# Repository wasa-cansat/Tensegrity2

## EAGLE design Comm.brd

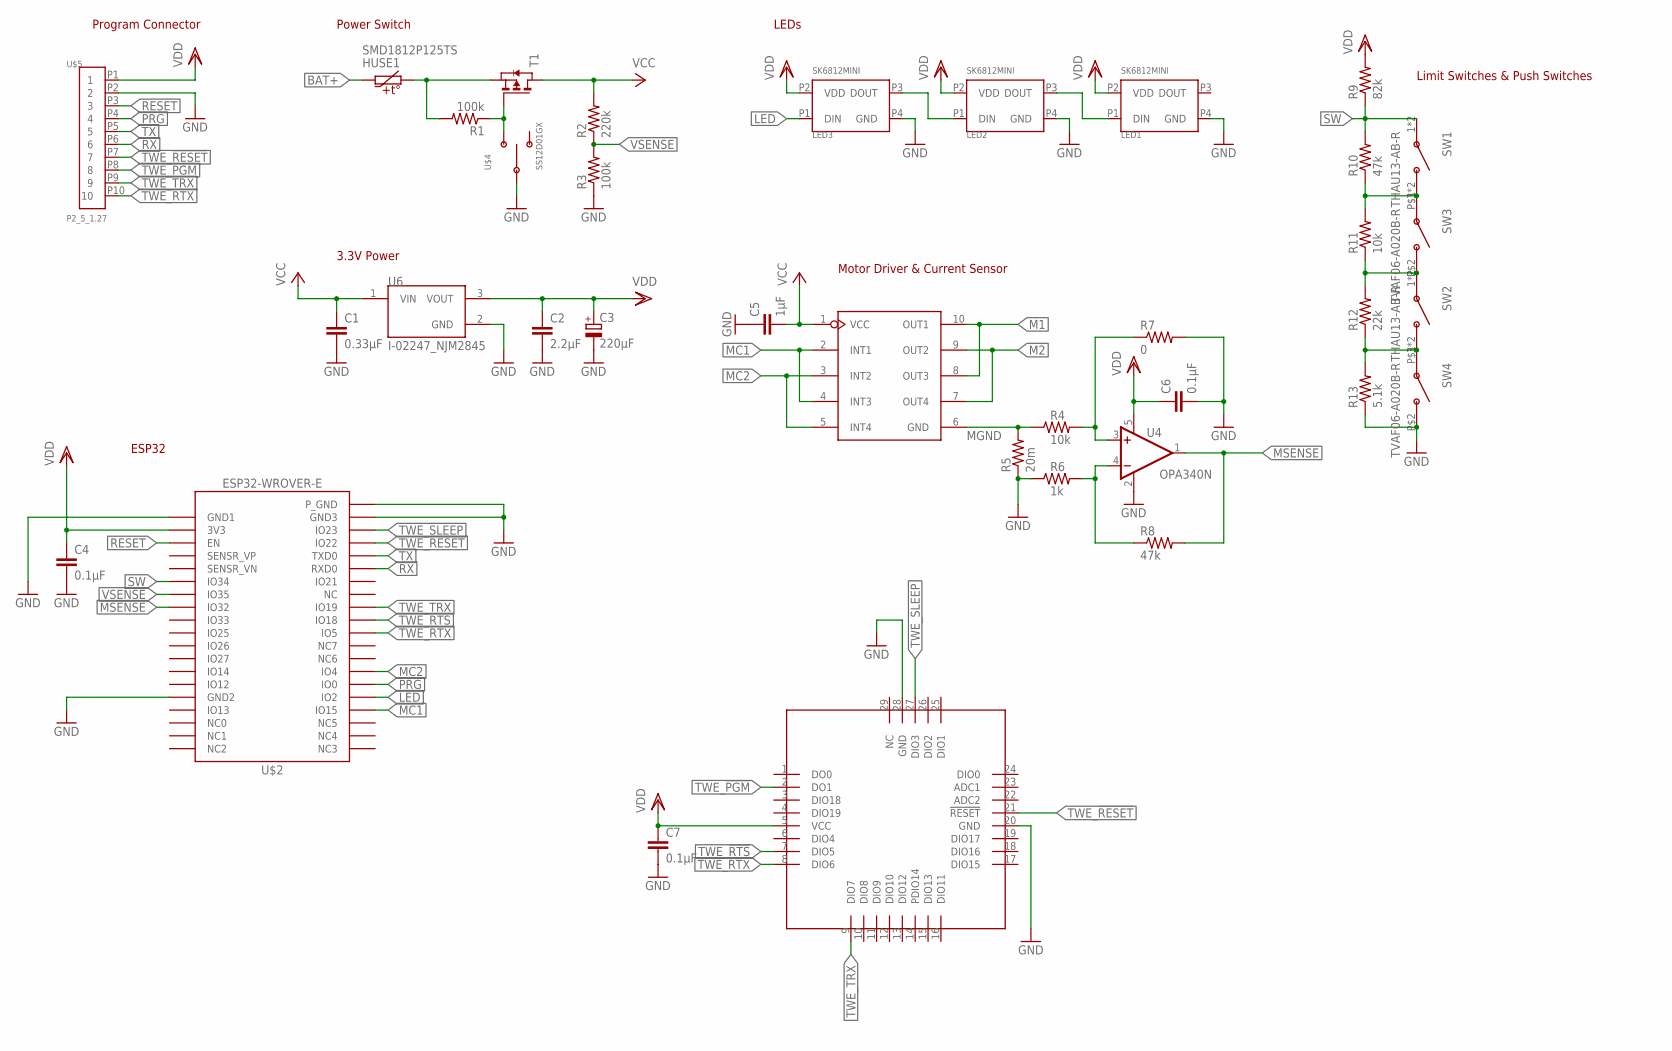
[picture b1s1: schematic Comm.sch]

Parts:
C1: 0.33µF; C0603
C2: 2.2µF; C0603
C3: 220µF; UD-6,3X7,7_NICHICON
C4, C6: 0.1µF; C0603
C5: 1µF; C0603
C7: 0.1µF; C0603K
HUSE1: SMD1812P125TS; SMD1812P
LED1, LED2, LED3: SK6812MINI; SK68XXMINI
R1, R3: 100k; R0603
R2: 220k; R0603
R4, R11: 10k; R0603
R5: 20m; R6332W
R6: 1k; R0603
R7: 0; R0603
R8, R10: 47k; R0603
R9: 82k; R0603
R12: 22k; R0603
R13: 5.1k; R0603
SW1, SW2: THAU13-AB-R
SW3, SW4: TVAF06-A020B-R
T1: PMOSSOT23; SOT-23
TWE-LITE: LITE
U4: OPA340N; SOT23-5
U5: DRIVER-LV8548MC-AH(SOIC10); SOIC10-1.0-5X4MM
U6: I-02247_NJM2845; TO252
U$2: ESP32-WROVER-E
U$4: SS12D01GX
U$5: P2_5_1.27

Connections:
BAT+: HUSE1.1
GND: C1.2, C2.2, C3.-, C4.2, C5.1, C6.2, C7.2, LED1.P4 (GND), LED2.P4 (GND), LED3.P4 (GND), R3.1, R5.1, R6.1, R7.2, R13.1, SW4.P$2 (B), TWE-LITE.20 (GND), TWE-LITE.28 (GND), U4.2 (V-), U6.2 (GND), U$2.GND1, U$2.GND2, U$2.GND3, U$2.P_GND, U$4.2 (C), U$5.P2 (2)
LED: LED3.P1 (DIN), U$2.IO2
M1: U5.8 (OUT3), U5.10 (OUT1)
M2: U5.7 (OUT4), U5.9 (OUT2)
MC1: U5.2 (INT1), U5.4 (INT3), U$2.IO15
MC2: U5.3 (INT2), U5.5 (INT4), U$2.IO4
MGND: R4.1, R5.2, U5.6 (GND)
MSENSE: R8.2, U4.1 (OUT), U$2.IO32
unnamed: HUSE1.2, R1.2, T1.2 (S)
unnamed: R6.2, R8.1, U4.4 (-IN)
unnamed: R4.2, R7.1, U4.3 (+IN)
unnamed: R1.1, T1.3 (G), U$4.1 (A)
unnamed: LED2.P1 (DIN), LED3.P3 (DOUT)
unnamed: LED1.P1 (DIN), LED2.P3 (DOUT)
unnamed: R11.1, R12.2, SW2.1 (A), SW2.2 (A), SW3.P$2 (B)
unnamed: R10.1, R11.2, SW1.3 (B), SW1.4 (B), SW3.P$1 (A)
unnamed: R12.1, R13.2, SW2.3 (B), SW2.4 (B), SW4.P$1 (A)
PRG: U$2.IO0, U$5.P4 (4)
RESET: U$2.EN, U$5.P3 (3)
RX: U$2.RXD0, U$5.P6 (6)
SW: R9.1, R10.2, SW1.1 (A), SW1.2 (A), U$2.IO34
TWE_!PGM!: TWE-LITE.2 (DO1), U$5.P8 (8)
TWE_!RESET!: TWE-LITE.21 (!RESET!), U$2.IO22, U$5.P7 (7)
TWE_!RTS!: TWE-LITE.7 (DIO5), U$2.IO18
TWE_RTX: TWE-LITE.8 (DIO6), U$2.IO5, U$5.P10 (10)
TWE_SLEEP: TWE-LITE.27 (DIO3), U$2.IO23
TWE_TRX: TWE-LITE.9 (DIO7), U$2.IO19, U$5.P9 (9)
TX: U$2.TXD0, U$5.P5 (5)
VCC: C1.1, C5.2, R2.2, T1.1 (D), U5.1 (VCC), U6.1 (VIN)
VDD: C2.1, C3.+, C4.1, C6.1, C7.1, LED1.P2 (VDD), LED2.P2 (VDD), LED3.P2 (VDD), R9.2, TWE-LITE.5 (VCC), U4.5 (V+), U6.3 (VOUT), U$2.3V3, U$5.P1 (1)
VSENSE: R2.1, R3.2, U$2.IO35

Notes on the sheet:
Program Connector
Power Switch
3.3V Power
Motor Driver & Current Sensor
ESP32
LEDs
Limit Switches & Push Switches

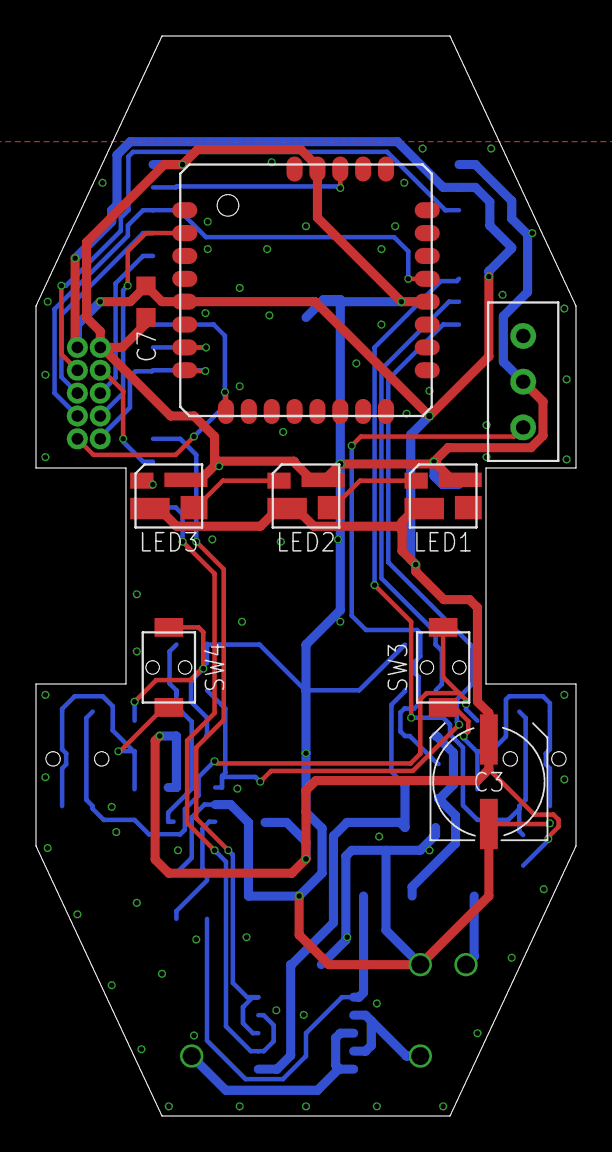
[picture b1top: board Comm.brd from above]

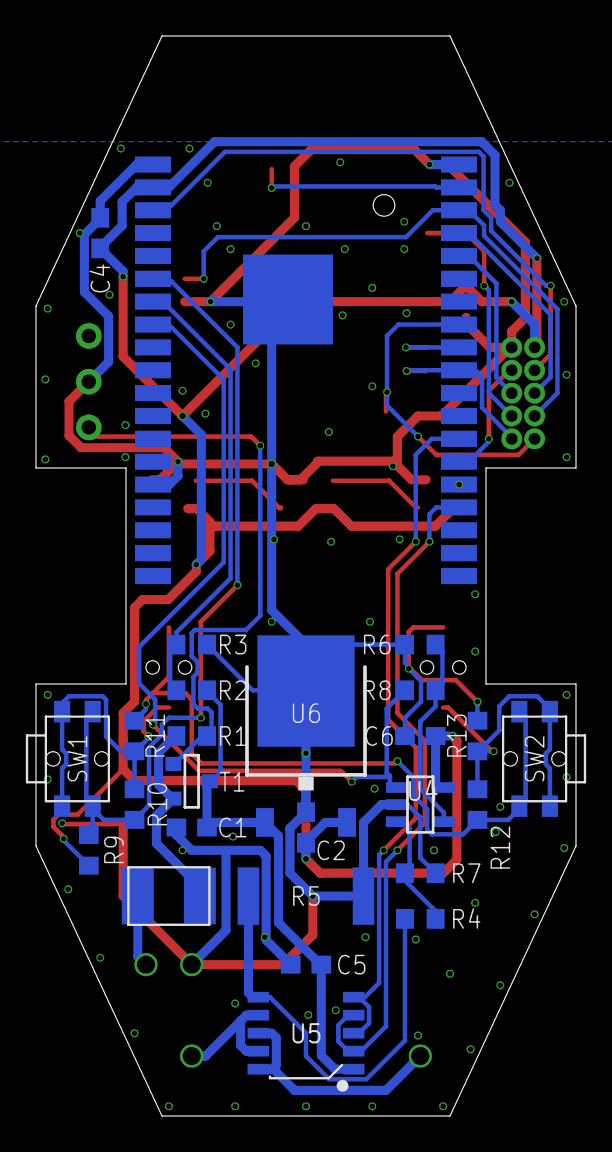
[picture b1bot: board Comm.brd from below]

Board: 2 copper layers, 30.0 x 60.0 mm, 36 parts (26 on the bottom side), 31 nets.

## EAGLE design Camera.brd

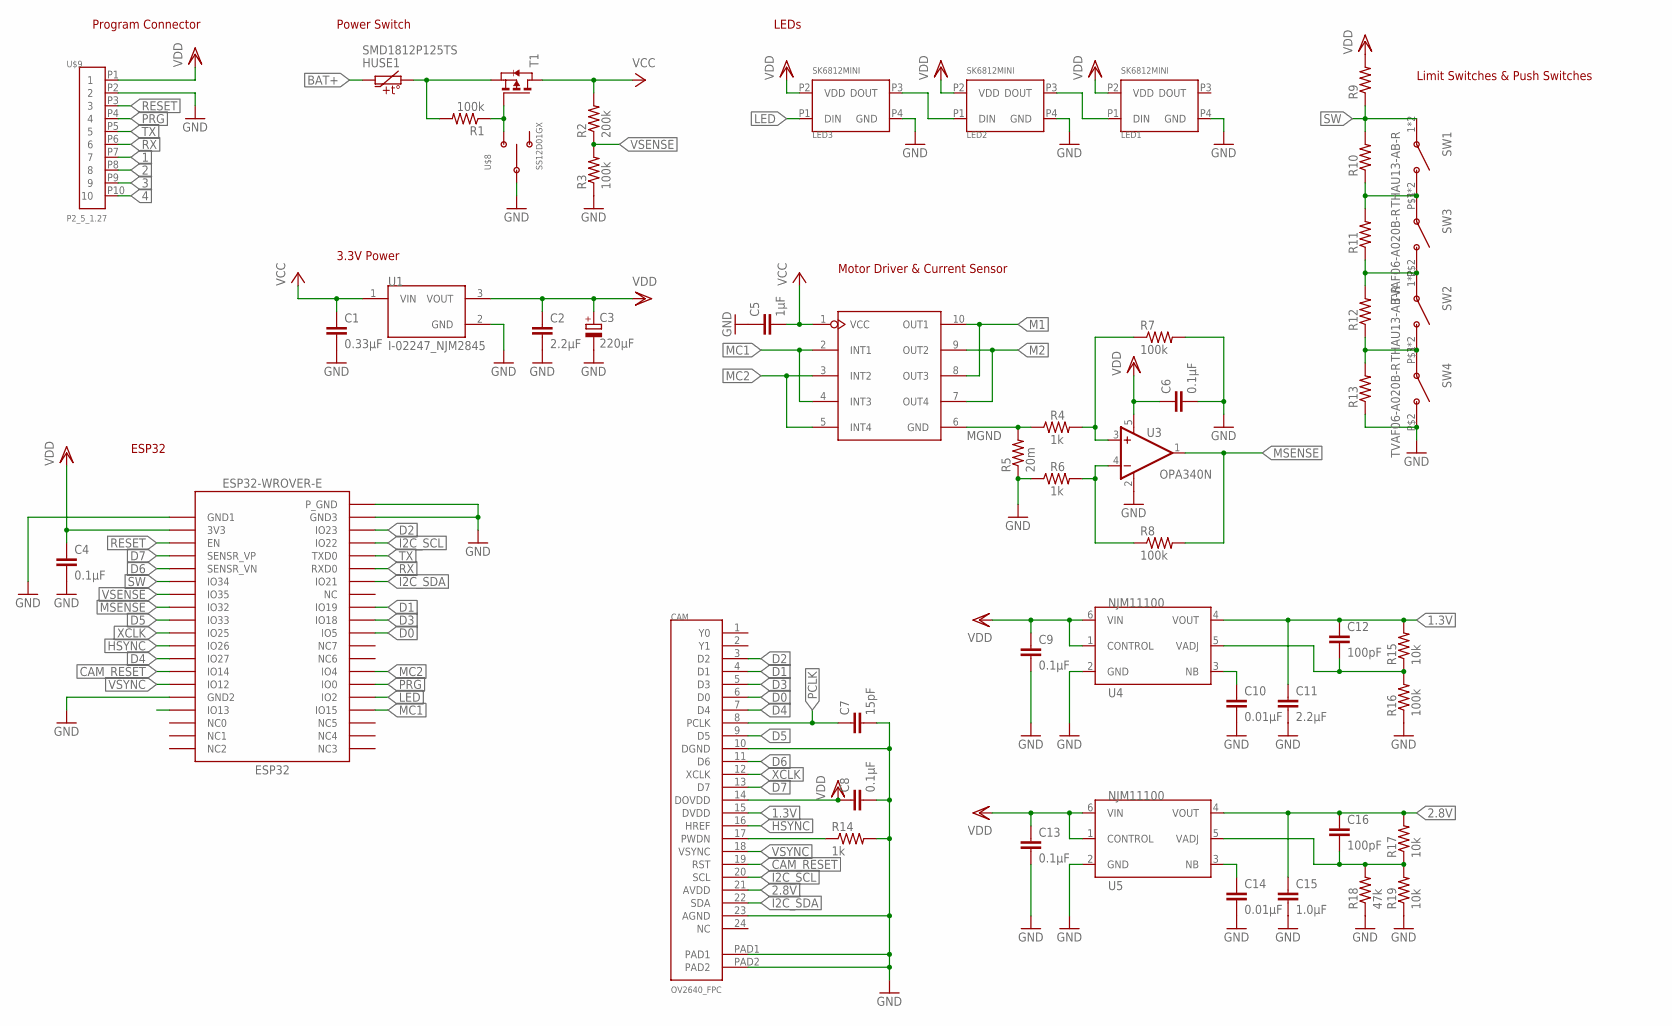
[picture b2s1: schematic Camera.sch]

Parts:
C1: 0.33µF; C0603
C2, C11: 2.2µF; C0603
C3: 220µF; UD-6,3X7,7_NICHICON
C4, C6, C8, C9, C13: 0.1µF; C0603
C5: 1µF; C0603
C7: 15pF; C0603
C10, C14: 0.01µF; C0603
C12, C16: 100pF; C0603
C15: 1.0µF; C0603
CAM: OV2640_FPC; FH12-24S-0.5SH
ESP32: ESP32-WROVER-E
HUSE1: SMD1812P125TS; SMD1812P
LED1, LED2, LED3: SK6812MINI; SK68XXMINI
R1, R3, R7, R8, R16: 100k; R0603
R2: 200k; R0603
R4, R6, R14: 1k; R0603
R5: 20m; R6332W
R9, R10, R11, R12, R13: R-US_R0603; R0603
R15, R17, R19: 10k; R0603
R18: 47k; R0603
SW1, SW2: THAU13-AB-R
SW3, SW4: TVAF06-A020B-R
T1: PMOSSOT23; SOT-23
U1: I-02247_NJM2845; TO252
U2: DRIVER-LV8548MC-AH(SOIC10); SOIC10-1.0-5X4MM
U3: OPA340N; SOT23-5
U4, U5: NJM11100; SOT95P240X110-6N
U$8: SS12D01GX
U$9: P2_5_1.27

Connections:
1: U$9.P7 (7)
1.3V: C11.1, C12.1, CAM.15 (DVDD), R15.2, U4.4 (VOUT)
2: U$9.P8 (8)
2.8V: C15.1, C16.1, CAM.21 (AVDD), R17.2, U5.4 (VOUT)
3: U$9.P9 (9)
4: U$9.P10 (10)
BAT+: HUSE1.1
CAM_RESET: CAM.19 (RST), ESP32.IO14
D0: CAM.6 (D0), ESP32.IO5
D1: CAM.4 (D1), ESP32.IO19
D2: CAM.3 (D2), ESP32.IO23
D3: CAM.5 (D3), ESP32.IO18
D4: CAM.7 (D4), ESP32.IO27
D5: CAM.9 (D5), ESP32.IO33
D6: CAM.11 (D6), ESP32.SENSOR_VN (SENSR_VN)
D7: CAM.13 (D7), ESP32.SENSOR_VP (SENSR_VP)
GND: C1.2, C2.2, C3.-, C4.2, C5.1, C6.2, C7.2, C8.2, C9.2, C10.2, C11.2, C13.2, C14.2, C15.2, CAM.10 (DGND), CAM.23 (AGND), CAM.PAD1, CAM.PAD2, ESP32.GND1, ESP32.GND2, ESP32.GND3, ESP32.P_GND, LED1.P4 (GND), LED2.P4 (GND), LED3.P4 (GND), R3.1, R5.1, R6.1, R7.2, R13.1, R14.2, R16.1, R18.1, R19.1, SW4.P$2 (B), U1.2 (GND), U3.2 (V-), U4.2 (GND), U5.2 (GND), U$8.2 (C), U$9.P2 (2)
HSYNC: CAM.16 (HREF), ESP32.IO26
I2C_SCL: CAM.20 (SCL), ESP32.IO22
I2C_SDA: CAM.22 (SDA), ESP32.IO21
LED: ESP32.IO2, LED3.P1 (DIN)
M1: U2.8 (OUT3), U2.10 (OUT1)
M2: U2.7 (OUT4), U2.9 (OUT2)
MC1: ESP32.IO15, U2.2 (INT1), U2.4 (INT3)
MC2: ESP32.IO4, U2.3 (INT2), U2.5 (INT4)
MGND: R4.1, R5.2, U2.6 (GND)
MSENSE: ESP32.IO32, R8.2, U3.1 (OUT)
unnamed: C10.1, U4.3 (NB)
unnamed: C12.2, R15.1, R16.2, U4.5 (VADJ)
unnamed: C14.1, U5.3 (NB)
unnamed: C16.2, R17.1, R18.2, R19.2, U5.5 (VADJ)
unnamed: CAM.17 (PWDN), R14.1
unnamed: HUSE1.2, R1.2, T1.2 (S)
unnamed: R6.2, R8.1, U3.4 (-IN)
unnamed: R4.2, R7.1, U3.3 (+IN)
unnamed: R1.1, T1.3 (G), U$8.1 (A)
unnamed: LED2.P1 (DIN), LED3.P3 (DOUT)
unnamed: LED1.P1 (DIN), LED2.P3 (DOUT)
unnamed: R11.1, R12.2, SW2.1 (A), SW2.2 (A), SW3.P$2 (B)
unnamed: R10.1, R11.2, SW1.3 (B), SW1.4 (B), SW3.P$1 (A)
unnamed: R12.1, R13.2, SW2.3 (B), SW2.4 (B), SW4.P$1 (A)
PCLK: C7.1, CAM.8 (PCLK)
PRG: ESP32.IO0, U$9.P4 (4)
RESET: ESP32.EN, U$9.P3 (3)
RX: ESP32.RXD0, U$9.P6 (6)
SW: ESP32.IO34, R9.1, R10.2, SW1.1 (A), SW1.2 (A)
TX: ESP32.TXD0, U$9.P5 (5)
VCC: C1.1, C5.2, R2.2, T1.1 (D), U1.1 (VIN), U2.1 (VCC)
VDD: C2.1, C3.+, C4.1, C6.1, C8.1, C9.1, C13.1, CAM.14 (DOVDD), ESP32.3V3, LED1.P2 (VDD), LED2.P2 (VDD), LED3.P2 (VDD), R9.2, U1.3 (VOUT), U3.5 (V+), U4.1 (CONTROL), U4.6 (VIN), U5.1 (CONTROL), U5.6 (VIN), U$9.P1 (1)
VSENSE: ESP32.IO35, R2.1, R3.2
VSYNC: CAM.18 (VSYNC), ESP32.IO12
XCLK: CAM.12 (XCLK), ESP32.IO25

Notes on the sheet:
Program Connector
Power Switch
3.3V Power
Motor Driver & Current Sensor
ESP32
LEDs
Limit Switches & Push Switches

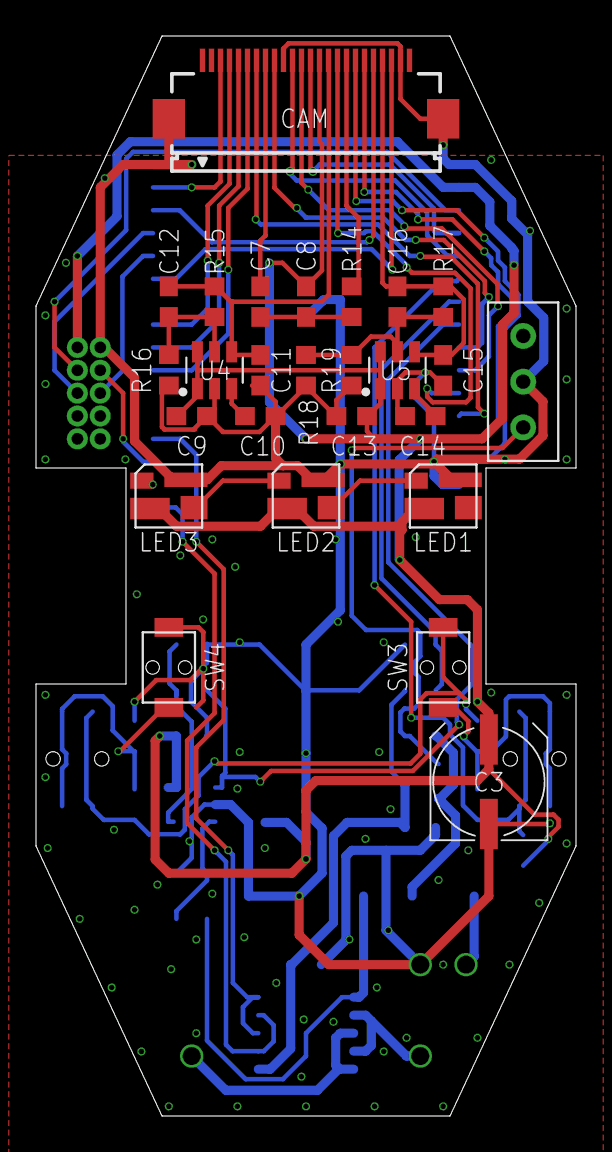
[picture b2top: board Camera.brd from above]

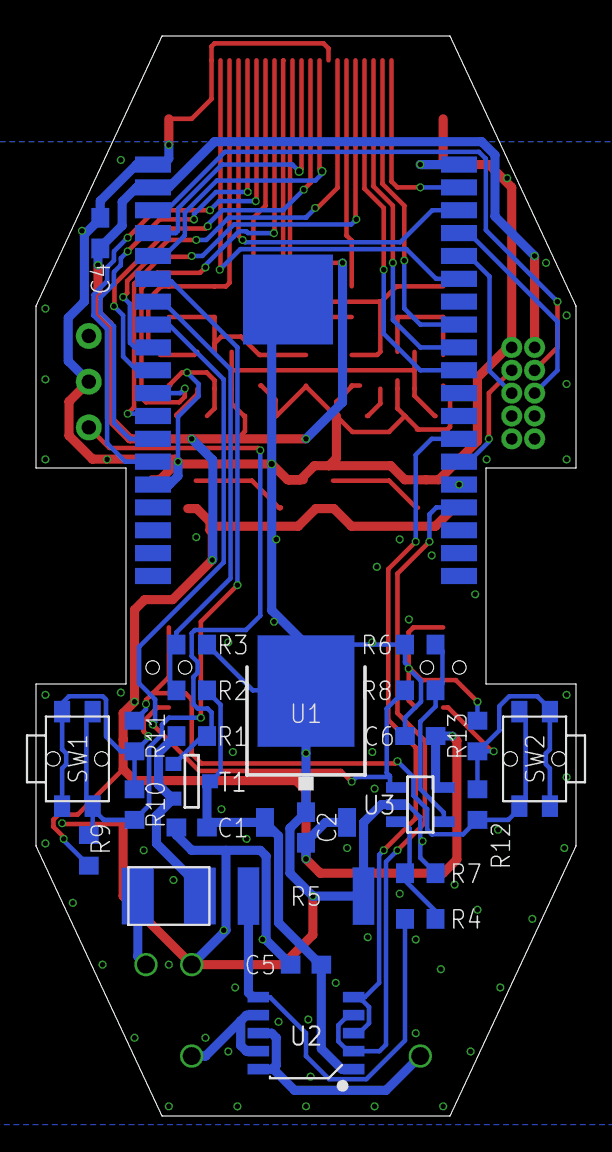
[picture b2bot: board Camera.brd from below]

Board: 2 copper layers, 30.0 x 60.0 mm, 53 parts (26 on the bottom side), 47 nets.

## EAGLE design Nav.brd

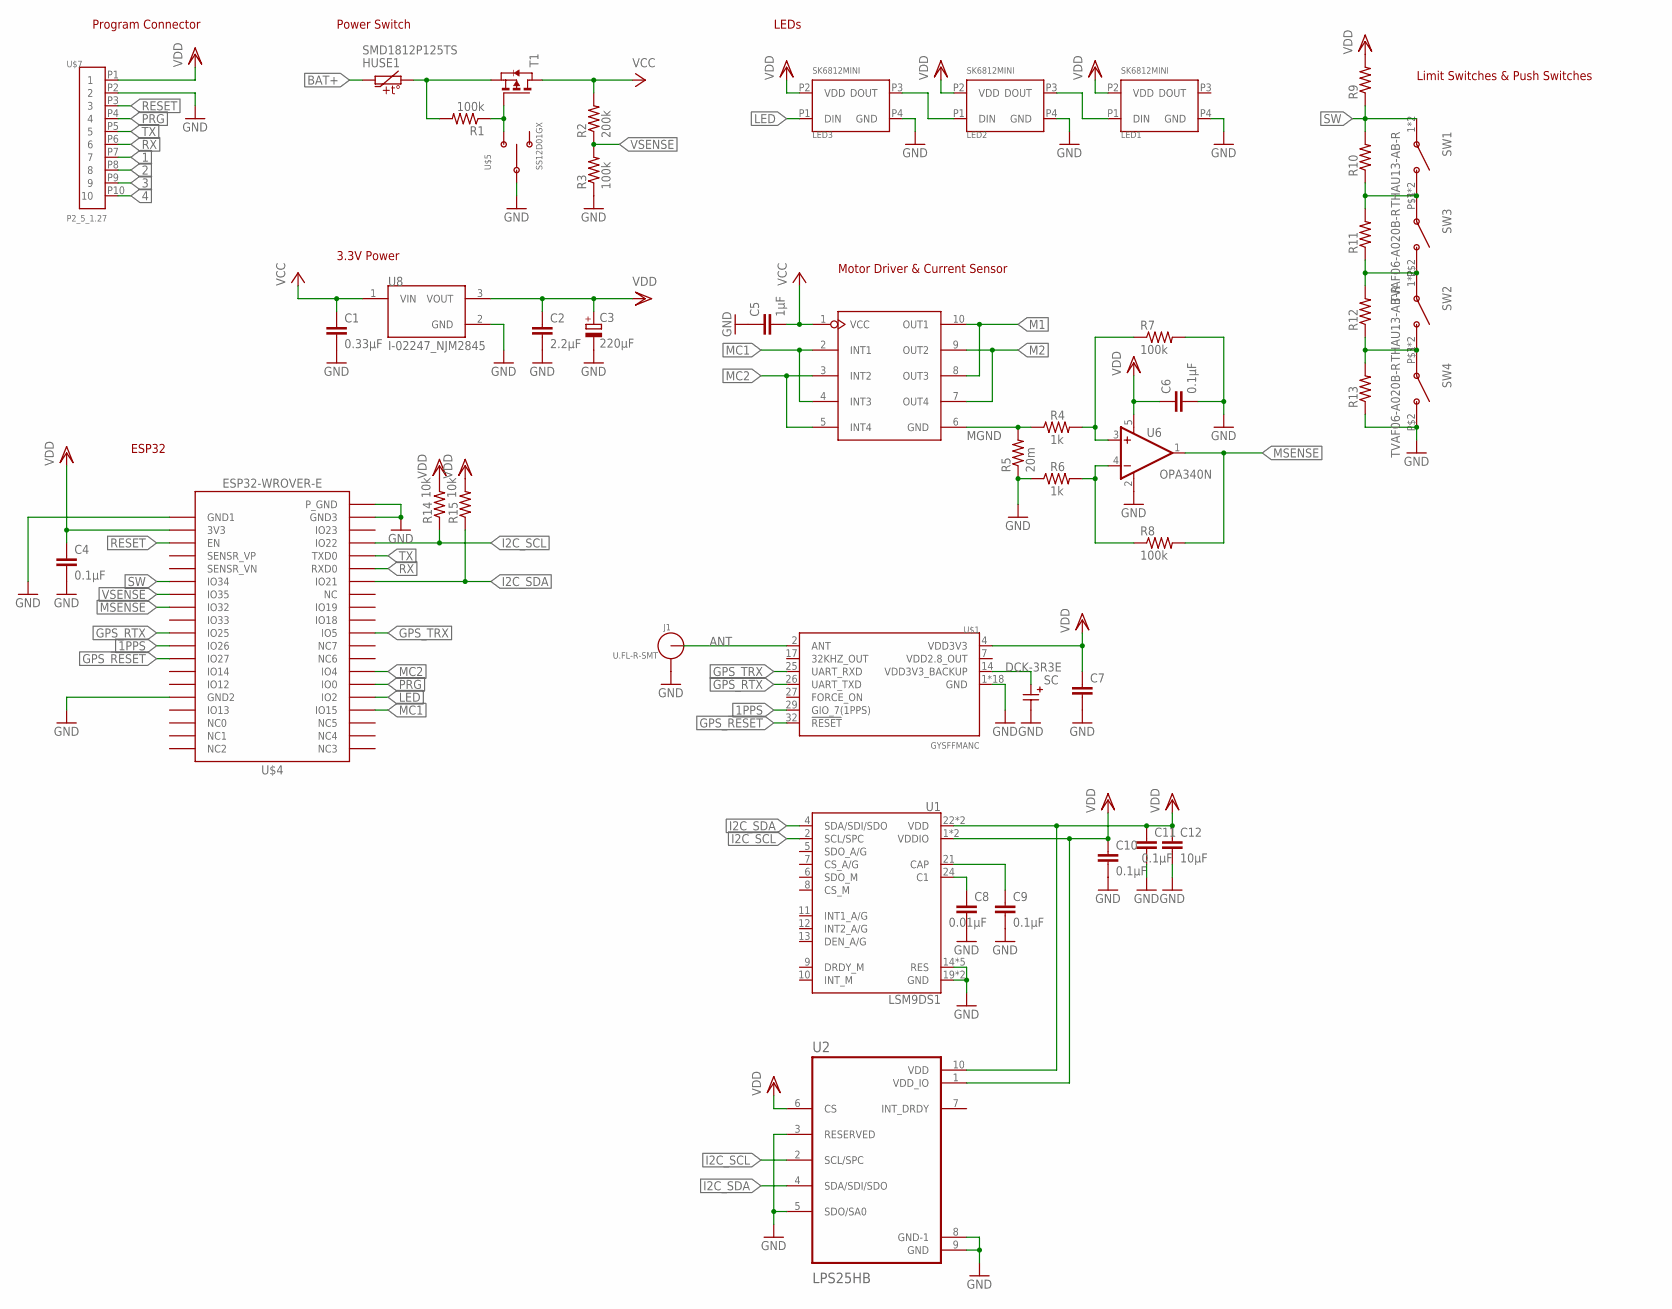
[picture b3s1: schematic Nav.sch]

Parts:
C1: 0.33µF; C0603
C2: 2.2µF; C0603
C3: 220µF; UD-6,3X7,7_NICHICON
C4, C6, C9, C10, C11: 0.1µF; C0603
C5: 1µF; C0603
C7: C-EUC0603; C0603
C8: 0.01µF; C0603
C12: 10µF; C0603
HUSE1: SMD1812P125TS; SMD1812P
J1: U.FL-R-SMT; U.FL_SMT
LED1, LED2, LED3: SK6812MINI; SK68XXMINI
R1, R3, R7, R8: 100k; R0603
R2: 200k; R0603
R4, R6: 1k; R0603
R5: 20m; R6332W
R9, R10, R11, R12, R13: R-US_R0603; R0603
R14, R15: 10k; R0603
SC: DCK-3R3E; DC,DCK
SW1, SW2: THAU13-AB-R
SW3, SW4: TVAF06-A020B-R
T1: PMOSSOT23; SOT-23
U1: LSM9DS1; LGA24-8X4
U2: LPS25HB; PQFN60P250X250X80-10N
U6: OPA340N; SOT23-5
U7: DRIVER-LV8548MC-AH(SOIC10); SOIC10-1.0-5X4MM
U8: I-02247_NJM2845; TO252
U$1: GYSFFMANC
U$4: ESP32-WROVER-E
U$5: SS12D01GX
U$7: P2_5_1.27

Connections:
1: U$7.P7 (7)
1PPS: U$1.29 (GIO_7(1PPS)), U$4.IO26
2: U$7.P8 (8)
3: U$7.P9 (9)
4: U$7.P10 (10)
ANT: J1.SIG (ANT), U$1.2 (ANT)
BAT+: HUSE1.1
GND: C1.2, C2.2, C3.-, C4.2, C5.1, C6.2, C7.2, C8.2, C9.2, C10.2, C11.2, C12.2, J1.GND1, J1.GND2, LED1.P4 (GND), LED2.P4 (GND), LED3.P4 (GND), R3.1, R5.1, R6.1, R7.2, R13.1, SC.-, SW4.P$2 (B), U1.14 (RES), U1.15 (RES), U1.16 (RES), U1.17 (RES), U1.18 (RES), U1.19 (GND), U1.20 (GND), U2.3 (RESERVED), U2.5 (SDO/SA0), U2.8 (GND-1), U2.9 (GND), U6.2 (V-), U8.2 (GND), U$1.1 (GND), U$1.3 (GND), U$1.8 (GND), U$1.10 (GND), U$1.12 (GND), U$1.22 (GND), U$1.33 (GND), U$1.36 (GND), U$1.37 (GND), U$1.38 (GND), U$1.39 (GND), U$1.40 (GND), U$1.41 (GND), U$1.42 (GND), U$1.43 (GND), U$1.44 (GND), U$1.45 (GND), U$1.46 (GND), U$4.GND1, U$4.GND2, U$4.GND3, U$4.P_GND, U$5.2 (C), U$7.P2 (2)
GPS_!RESET!: U$1.32 (!RESET!), U$4.IO27
GPS_RTX: U$1.26 (UART_TXD), U$4.IO25
GPS_TRX: U$1.25 (UART_RXD), U$4.IO5
I2C_SCL: R14.1, U1.2 (SCL/SPC), U2.2 (SCL/SPC), U$4.IO22
I2C_SDA: R15.1, U1.4 (SDA/SDI/SDO), U2.4 (SDA/SDI/SDO), U$4.IO21
LED: LED3.P1 (DIN), U$4.IO2
M1: U7.8 (OUT3), U7.10 (OUT1)
M2: U7.7 (OUT4), U7.9 (OUT2)
MC1: U7.2 (INT1), U7.4 (INT3), U$4.IO15
MC2: U7.3 (INT2), U7.5 (INT4), U$4.IO4
MGND: R4.1, R5.2, U7.6 (GND)
MSENSE: R8.2, U6.1 (OUT), U$4.IO32
unnamed: SC.+, U$1.14 (VDD3V3_BACKUP)
unnamed: C8.1, U1.24 (C1)
unnamed: C9.1, U1.21 (CAP)
unnamed: HUSE1.2, R1.2, T1.2 (S)
unnamed: R6.2, R8.1, U6.4 (-IN)
unnamed: R4.2, R7.1, U6.3 (+IN)
unnamed: R1.1, T1.3 (G), U$5.1 (A)
unnamed: LED2.P1 (DIN), LED3.P3 (DOUT)
unnamed: LED1.P1 (DIN), LED2.P3 (DOUT)
unnamed: R11.1, R12.2, SW2.1 (A), SW2.2 (A), SW3.P$2 (B)
unnamed: R10.1, R11.2, SW1.3 (B), SW1.4 (B), SW3.P$1 (A)
unnamed: R12.1, R13.2, SW2.3 (B), SW2.4 (B), SW4.P$1 (A)
PRG: U$4.IO0, U$7.P4 (4)
RESET: U$4.EN, U$7.P3 (3)
RX: U$4.RXD0, U$7.P6 (6)
SW: R9.1, R10.2, SW1.1 (A), SW1.2 (A), U$4.IO34
TX: U$4.TXD0, U$7.P5 (5)
VCC: C1.1, C5.2, R2.2, T1.1 (D), U7.1 (VCC), U8.1 (VIN)
VDD: C2.1, C3.+, C4.1, C6.1, C7.1, C10.1, C11.1, C12.1, LED1.P2 (VDD), LED2.P2 (VDD), LED3.P2 (VDD), R9.2, R14.2, R15.2, U1.1 (VDDIO), U1.3 (VDDIO), U1.22 (VDD), U1.23 (VDD), U2.1 (VDD_IO), U2.6 (CS), U2.10 (VDD), U6.5 (V+), U8.3 (VOUT), U$1.4 (VDD3V3), U$4.3V3, U$7.P1 (1)
VDD2.8_OUT: U$1.7 (VDD2.8_OUT)
VSENSE: R2.1, R3.2, U$4.IO35

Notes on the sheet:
Program Connector
Power Switch
3.3V Power
Motor Driver & Current Sensor
ESP32
LEDs
Limit Switches & Push Switches

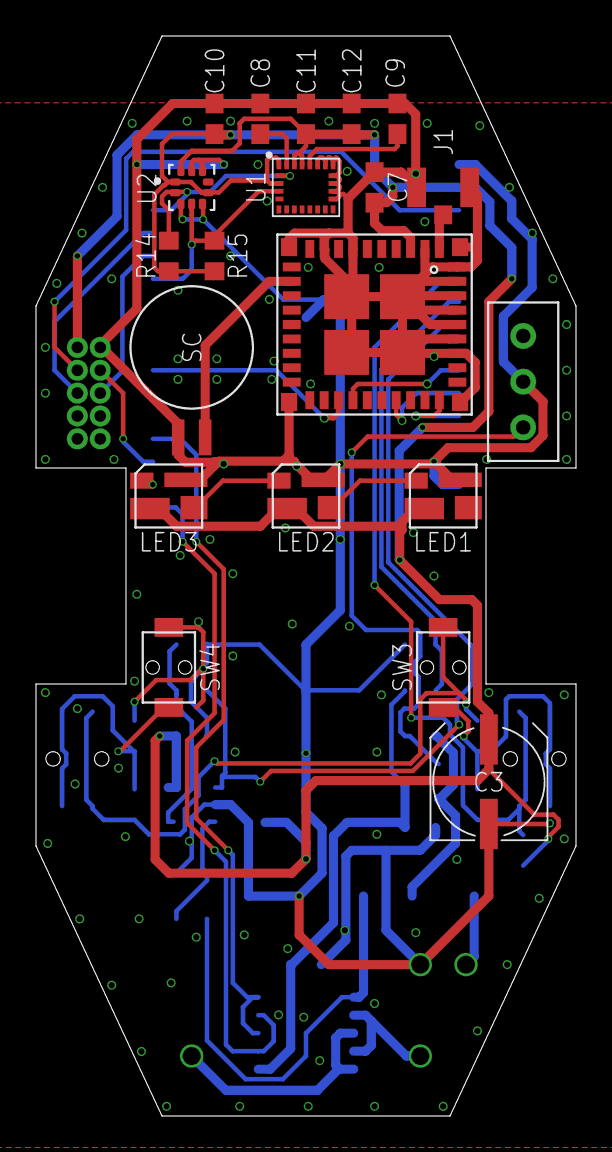
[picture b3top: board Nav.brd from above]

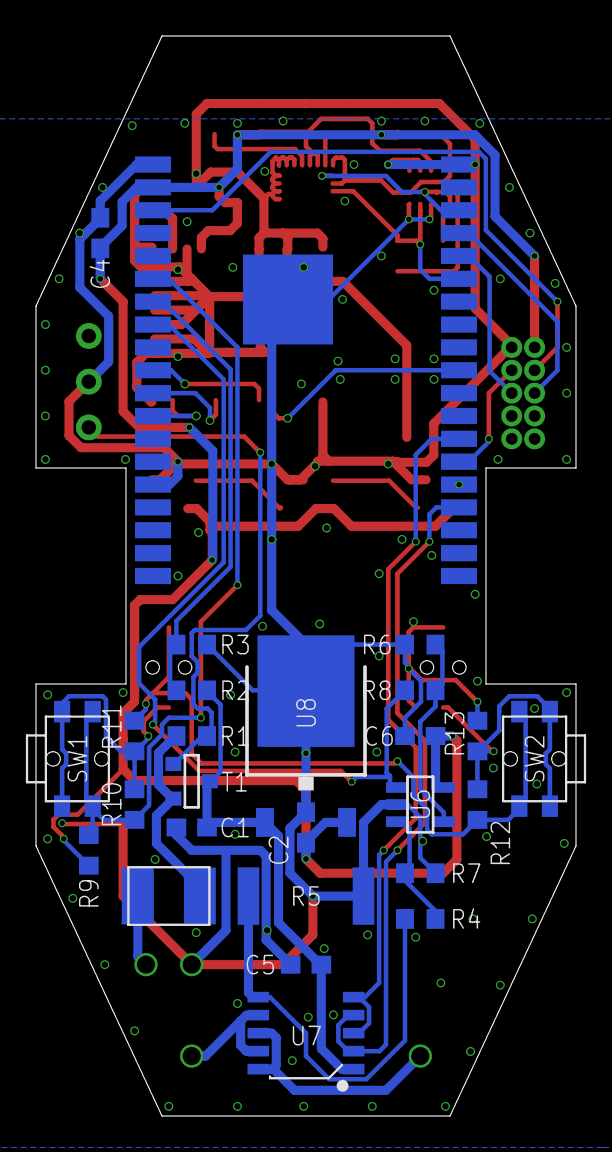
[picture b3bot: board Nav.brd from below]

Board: 2 copper layers, 30.0 x 60.0 mm, 47 parts (26 on the bottom side), 35 nets.

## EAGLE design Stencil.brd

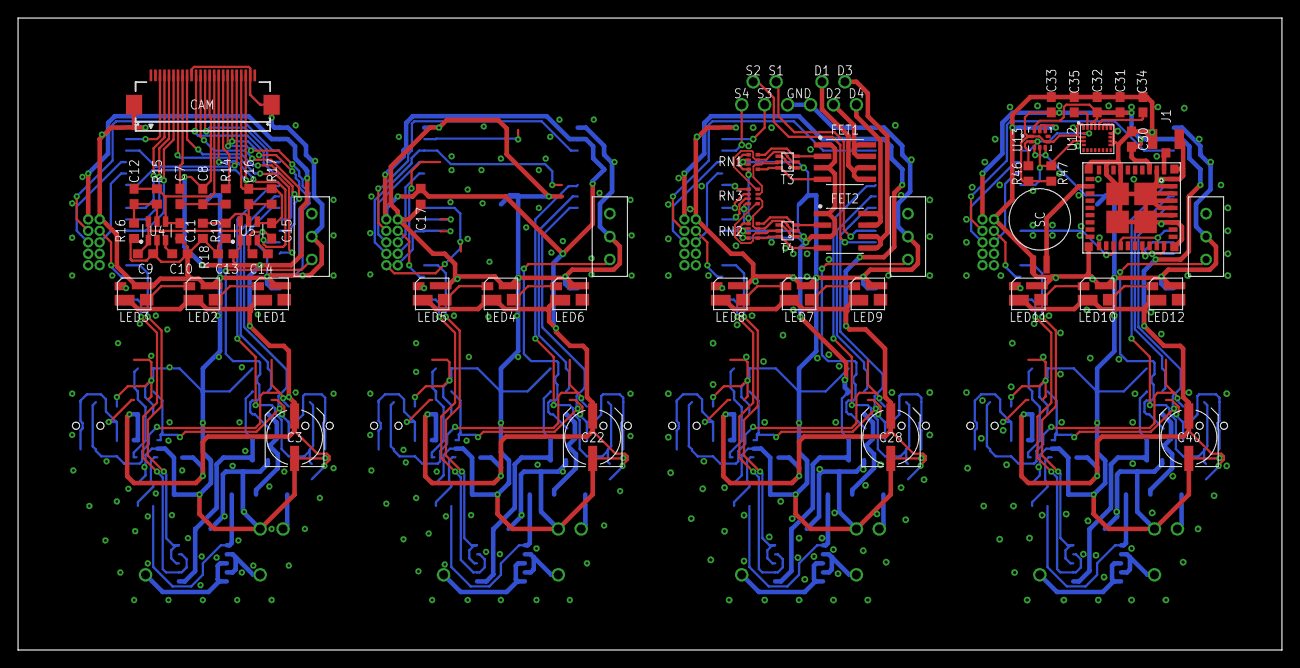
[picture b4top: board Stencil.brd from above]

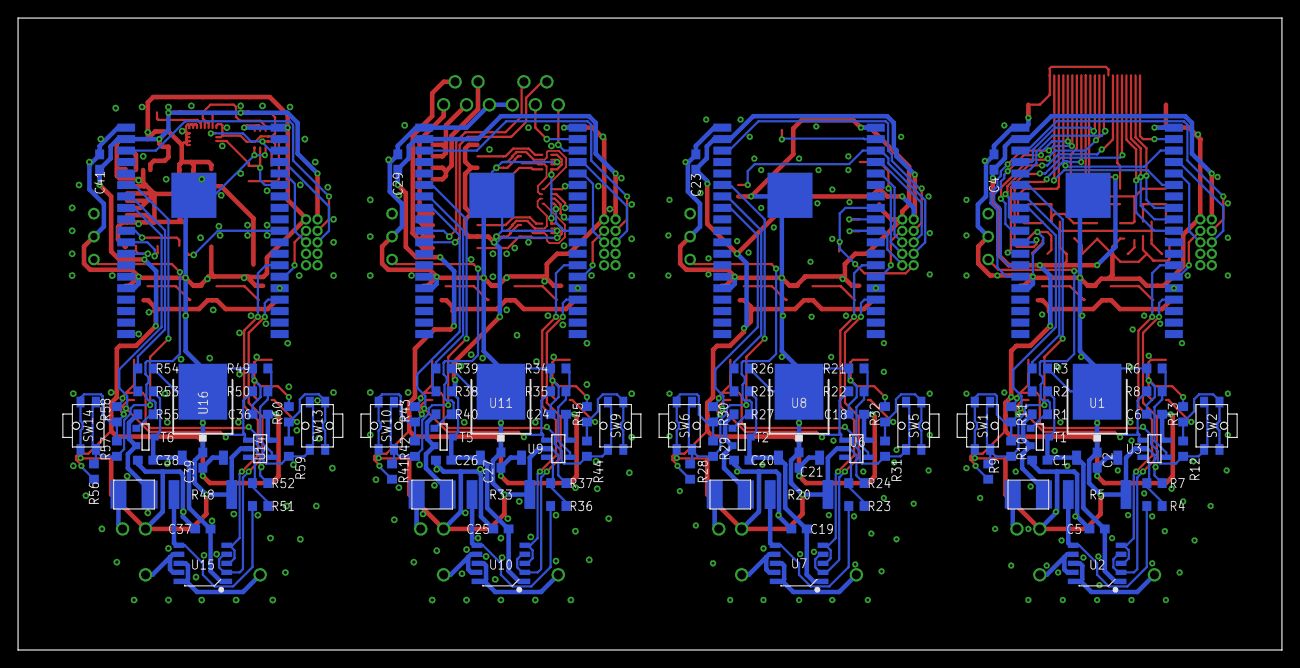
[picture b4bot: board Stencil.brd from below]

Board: 2 copper layers, 140.0 x 70.0 mm, 168 parts (104 on the bottom side), 151 nets.

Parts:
C1, C20, C26, C38: 0.33µF; C0603
C2, C11, C21, C27, C39: 2.2µF; C0603
C3, C22, C28, C40: 220µF; UD-6,3X7,7_NICHICON
C4, C6, C8, C9, C13, C18, C23, C24, C29, C32, C33, C34, C36, C41: 0.1µF; C0603
C5, C19, C25, C37: 1µF; C0603
C7: 15pF; C0603
C10, C14, C35: 0.01µF; C0603
C12, C16: 100pF; C0603
C15: 1.0µF; C0603
C17: 0.1µF; C0603K
C30: C0603
C31: 10µF; C0603
CAM: OV2640_FPC; FH12-24S-0.5SH
ESP32: ESP32-WROVER-E
FET1, FET2: FDS4935A; SOIC127P600X175-8N
HUSE1, HUSE2, HUSE3, HUSE4: SMD1812P125TS; SMD1812P
J1: U.FL-R-SMT; U.FL_SMT
LED1, LED2, LED3, LED4, LED5, LED6, LED7, LED8, LED9, LED10, LED11, LED12: SK6812MINI; SK68XXMINI
R1, R3, R7, R8, R16, R22, R24, R26, R27, R35, R37, R39, R40, R50, R52, R54, R55: 100k; R0603
R2, R25, R38, R53: 200k; R0603
R4, R6, R14, R21, R23, R34, R36, R49, R51: 1k; R0603
R5, R20, R33, R48: 20m; R6332W
R9, R10, R11, R12, R13, R28, R29, R30, R31, R32, R41, R42, R43, R44, R45, R56, R57, R58, R59, R60: R0603
R15, R17, R19, R46, R47: 10k; R0603
R18: 47k; R0603
RN1, RN2, RN3: 10k; 4X0402ARV341
SC: DCK-3R3E; DC,DCK
SW1, SW2, SW5, SW6, SW9, SW10, SW13, SW14: THAU13-AB-R
T1, T2, T5, T6: SOT-23
T3, T4: HN1C01FU; SOT-363
U1, U8, U11, U16: I-02247_NJM2845; TO252
U2, U7, U10, U15: DRIVER-LV8548MC-AH(SOIC10); SOIC10-1.0-5X4MM
U3, U6, U9, U14: OPA340N; SOT23-5
U4, U5: NJM11100; SOT95P240X110-6N
U12: LSM9DS1; LGA24-8X4
U13: LPS25HB; PQFN60P250X250X80-10N
U$1, U$2, U$10: ESP32-WROVER-E
U$3, U$4, U$8, U$11: SS12D01GX
U$5, U$6, U$9, U$12: P2_5_1.27
U$7: GYSFFMANC

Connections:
1.3V: C11.1, C12.1, CAM.15, R15.2, U4.4
1PPS: U$7.29, U$10.IO26
2.8V: C15.1, C16.1, CAM.21, R17.2, U5.4
ANT: J1.SIG, U$7.2
C1: RN3.1, U$1.IO21
C2: RN3.2, U$1.IO19
C3: RN3.3, U$1.IO18
C4: RN3.4, U$1.IO5
CAM_RESET: CAM.19, ESP32.IO14
D0: CAM.6, ESP32.IO5
D1: CAM.4, ESP32.IO19
D2: CAM.3, ESP32.IO23
D3: CAM.5, ESP32.IO18
D4: CAM.7, ESP32.IO27
D5: CAM.9, ESP32.IO33
D6: CAM.11, ESP32.SENSOR_VN
D7: CAM.13, ESP32.SENSOR_VP
D8: FET1.5, FET1.6
D9: FET1.7, FET1.8
D10: FET2.5, FET2.6
D11: FET2.7, FET2.8
GND: C1.2, C2.2, C3.-, C4.2, C5.1, C6.2, C7.2, C8.2, C9.2, C10.2, C11.2, C13.2, C14.2, C15.2, CAM.10, CAM.23, CAM.PAD1, CAM.PAD2, ESP32.GND1, ESP32.GND2, ESP32.GND3, ESP32.P_GND, LED1.P4, LED2.P4, LED3.P4, R3.1, R5.1, R6.1, R7.2, R13.1, R14.2, R16.1, R18.1, R19.1, U1.2, U3.2, U4.2, U5.2, U$8.2, U$9.P2
GND1: C17.2, C18.2, C19.1, C20.2, C21.2, C22.-, C23.2, LED4.P4, LED5.P4, LED6.P4, R20.1, R21.1, R24.2, R26.1, R32.1, U6.2, U8.2, U$2.GND1, U$2.GND2, U$2.GND3, U$2.P_GND, U$4.2, U$5.P2
GND2: C24.2, C25.1, C26.2, C27.2, C28.-, C29.2, LED7.P4, LED8.P4, LED9.P4, R33.1, R34.1, R37.2, R39.1, R45.1, RN1.2, RN1.3, RN2.2, RN2.3, T3.1, T3.4, T4.1, T4.4, U9.2, U11.2, U$1.GND1, U$1.GND2, U$1.GND3, U$1.P_GND, U$3.2, U$6.P2
GND3: C30.2, C31.2, C32.2, C33.2, C34.2, C35.2, C36.2, C37.1, C38.2, C39.2, C40.-, C41.2, J1.GND1, J1.GND2, LED10.P4, LED11.P4, LED12.P4, R48.1, R49.1, R52.2, R54.1, R60.1, SC.-, U12.14, U12.15, U12.16, U12.17, U12.18, U12.19, U12.20, U13.3, U13.5, U13.8, U13.9, U14.2, U16.2, U$7.1, U$7.3, U$7.8, U$7.10, U$7.12, U$7.22, U$7.33, U$7.36, U$7.37, U$7.38, U$7.39, U$7.40, U$7.41, U$7.42, U$7.43, U$7.44, U$7.45, U$7.46, U$10.GND1, U$10.GND2, U$10.GND3, U$10.P_GND, U$11.2, U$12.P2
GPS_!RESET!: U$7.32, U$10.IO27
GPS_RTX: U$7.26, U$10.IO25
GPS_TRX: U$7.25, U$10.IO5
HSYNC: CAM.16, ESP32.IO26
I2C_SCL: CAM.20, ESP32.IO22
I2C_SCL1: R46.1, U12.2, U13.2, U$10.IO22
I2C_SDA: CAM.22, ESP32.IO21
I2C_SDA1: R47.1, U12.4, U13.4, U$10.IO21
LED: ESP32.IO2, LED3.P1
LED1: LED5.P1, U$2.IO2
LED2: LED8.P1, U$1.IO2
LED3: LED11.P1, U$10.IO2
M1: U2.8, U2.10
M2: U2.7, U2.9
M3: U7.8, U7.10
M4: U7.7, U7.9
M5: U10.8, U10.10
M6: U10.7, U10.9
M7: U15.8, U15.10
M8: U15.7, U15.9
MC1: ESP32.IO15, U2.2, U2.4
MC2: ESP32.IO4, U2.3, U2.5
MC3: U7.2, U7.4, U$2.IO15
MC4: U7.3, U7.5, U$2.IO4
MC5: U10.2, U10.4, U$1.IO15
MC6: U10.3, U10.5, U$1.IO4
MC7: U15.2, U15.4, U$10.IO15
MC8: U15.3, U15.5, U$10.IO4
MGND: R4.1, R5.2, U2.6
MGND1: R20.2, R23.1, U7.6
MGND2: R33.2, R36.1, U10.6
MGND3: R48.2, R51.1, U15.6
MSENSE: ESP32.IO32, R8.2, U3.1
MSENSE1: R22.2, U6.1, U$2.IO32
MSENSE2: R35.2, U9.1, U$1.IO32
MSENSE3: R50.2, U14.1, U$10.IO32
unnamed: C10.1, U4.3
unnamed: C12.2, R15.1, R16.2, U4.5
unnamed: C14.1, U5.3
unnamed: C16.2, R17.1, R18.2, R19.2, U5.5
unnamed: LED4.P1, LED5.P3
unnamed: LED4.P3, LED6.P1
unnamed: CAM.17, R14.1
unnamed: R30.1, R31.2, SW5.1, SW5.2
unnamed: HUSE2.2, R27.2, T2.2
unnamed: R21.2, R22.1, U6.4
unnamed: R23.2, R24.1, U6.3
unnamed: R27.1, T2.3, U$4.1
unnamed: HUSE1.2, R1.2, T1.2
unnamed: R6.2, R8.1, U3.4
unnamed: R4.2, R7.1, U3.3
unnamed: R1.1, T1.3, U$8.1
unnamed: LED2.P1, LED3.P3
unnamed: LED1.P1, LED2.P3
unnamed: R11.1, R12.2, SW2.1, SW2.2
unnamed: R10.1, R11.2, SW1.3, SW1.4
unnamed: R12.1, R13.2, SW2.3, SW2.4
unnamed: R29.1, R30.2, SW6.3, SW6.4
unnamed: R31.1, R32.2, SW5.3, SW5.4
unnamed: FET1.4, RN1.5, T3.6
unnamed: FET1.2, RN1.8, T3.3
unnamed: RN1.7, RN3.8, T3.2
unnamed: RN1.6, RN3.7, T3.5
unnamed: RN2.7, RN3.6, T4.2
unnamed: FET2.4, RN2.5, T4.6
unnamed: FET2.2, RN2.8, T4.3
unnamed: RN2.6, RN3.5, T4.5
unnamed: HUSE3.2, R40.2, T5.2
unnamed: R34.2, R35.1, U9.4
unnamed: R36.2, R37.1, U9.3
unnamed: R40.1, T5.3, U$3.1
unnamed: LED7.P1, LED8.P3
unnamed: LED7.P3, LED9.P1
unnamed: R43.1, R44.2, SW9.1, SW9.2
unnamed: R42.1, R43.2, SW10.3, SW10.4
unnamed: R44.1, R45.2, SW9.3, SW9.4
unnamed: SC.+, U$7.14
unnamed: C35.1, U12.24
unnamed: C34.1, U12.21
unnamed: HUSE4.2, R55.2, T6.2
unnamed: R49.2, R50.1, U14.4
unnamed: R51.2, R52.1, U14.3
unnamed: R55.1, T6.3, U$11.1
unnamed: LED10.P1, LED11.P3
unnamed: LED10.P3, LED12.P1
unnamed: R58.1, R59.2, SW13.1, SW13.2
unnamed: R57.1, R58.2, SW14.3, SW14.4
unnamed: R59.1, R60.2, SW13.3, SW13.4
PCLK: C7.1, CAM.8
PRG: ESP32.IO0, U$9.P4
PRG1: U$2.IO0, U$5.P4
PRG2: U$1.IO0, U$6.P4
PRG3: U$10.IO0, U$12.P4
RESET: ESP32.EN, U$9.P3
RESET1: U$2.EN, U$5.P3
RESET2: U$1.EN, U$6.P3
RESET3: U$10.EN, U$12.P3
RX: ESP32.RXD0, U$9.P6
RX1: U$2.RXD0, U$5.P6
RX2: U$1.RXD0, U$6.P6
RX3: U$10.RXD0, U$12.P6
SW: ESP32.IO34, R9.1, R10.2, SW1.1, SW1.2
SW1: R28.1, R29.2, SW6.1, SW6.2, U$2.IO34
SW2: R41.1, R42.2, SW10.1, SW10.2, U$1.IO34
SW3: R56.1, R57.2, SW14.1, SW14.2, U$10.IO34
TWE_!RESET!: U$2.IO22, U$5.P7
TWE_RTX: U$2.IO5, U$5.P10
TWE_TRX: U$2.IO19, U$5.P9
TX: ESP32.TXD0, U$9.P5
TX1: U$2.TXD0, U$5.P5
TX2: U$1.TXD0, U$6.P5
TX3: U$10.TXD0, U$12.P5
VCC: C1.1, C5.2, R2.2, T1.1, U1.1, U2.1
VCC1: C19.2, C20.1, R25.2, T2.1, U7.1, U8.1
VCC2: C25.2, C26.1, FET1.1, FET1.3, FET2.1, FET2.3, R38.2, RN1.1, RN1.4, RN2.1, RN2.4, T5.1, U10.1, U11.1
VCC3: C37.2, C38.1, R53.2, T6.1, U15.1, U16.1
VDD: C2.1, C3.+, C4.1, C6.1, C8.1, C9.1, C13.1, CAM.14, ESP32.3V3, LED1.P2, LED2.P2, LED3.P2, R9.2, U1.3, U3.5, U4.1, U4.6, U5.1, U5.6, U$9.P1
VDD1: C17.1, C18.1, C21.1, C22.+, C23.1, LED4.P2, LED5.P2, LED6.P2, R28.2, U6.5, U8.3, U$2.3V3, U$5.P1
VDD2: C24.1, C27.1, C28.+, C29.1, LED7.P2, LED8.P2, LED9.P2, R41.2, U9.5, U11.3, U$1.3V3, U$6.P1
VDD3: C30.1, C31.1, C32.1, C33.1, C36.1, C39.1, C40.+, C41.1, LED10.P2, LED11.P2, LED12.P2, R46.2, R47.2, R56.2, U12.1, U12.3, U12.22, U12.23, U13.1, U13.6, U13.10, U14.5, U16.3, U$7.4, U$10.3V3, U$12.P1
VSENSE: ESP32.IO35, R2.1, R3.2
VSENSE1: R25.1, R26.2, U$2.IO35
VSENSE2: R38.1, R39.2, U$1.IO35
VSENSE3: R53.1, R54.2, U$10.IO35
VSYNC: CAM.18, ESP32.IO12
XCLK: CAM.12, ESP32.IO25

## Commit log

2022-01-01 Make common block
2022-01-02 Add units
2022-01-08 Add sensors
2022-01-08 Deploy unit
2022-01-09 Communication unit
2022-01-09 Navigation unit
2022-01-10 Fix analog input pins
2022-01-10 reduce switch pins
2022-01-10 Camera Unit
2022-01-11 change parts name
2022-01-12 Format silk
2022-01-15 Add GND plane
2022-01-15 Add stencil
2022-02-12 add program
2022-02-12 voltage and current sensing
2022-02-21 Add nav unit
2022-02-22 Add message system
2022-02-23 Add GPS and IMU
2022-02-24 calculating attitude
2022-02-26 fix register value
